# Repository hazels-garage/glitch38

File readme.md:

# glitch38

just another sweep-alike using ergogen.

## features

* choc vertical spacing, mx horizontal
* 7305 millmax socket support for hotswap switches
* inner thumb rotated 90deg and spaced for 1.5u keycap
* oled
* tenting puck support

## non-reversable
I really dislike how reversable pcbs aren't always symetric.  One mcu might be flipped, oled screen or trrs jack is slightly off.  I'll eventually do a reversable pcb as I get better and can figure out ways to do it a way that doesn't bother me.

## materials
* 2x ProMicro or equivalent
* 2x PJ-320A TRRS Jack
* 2x SSD1306 OLED Screen (optional)
* 38x 1N4148 SOD-123 Diodes
* 38x Kailh Choc v1
* 74x 7305-0-15-15-47-27-10-0 Sockets (optional)
* 36-38x 1u Kailh Choc Keycaps
* 2x 1.5u Kailh Choc Keycaps (optional, for inner thumbs)

## notes
* promicros face up. so they'd be flat against the board if installing without a socket

## firmware
QMK link goes here

## future
* later revisions will likely start to incorporate battery support and then ZMK.
* maybe give choc minis a try
* EVQ encoder support

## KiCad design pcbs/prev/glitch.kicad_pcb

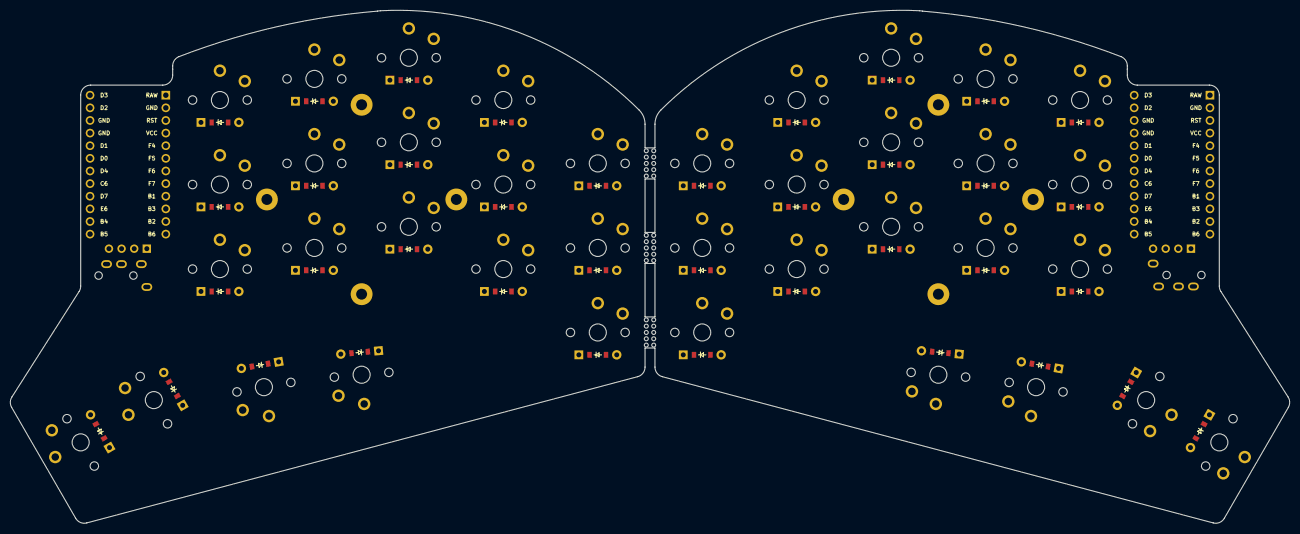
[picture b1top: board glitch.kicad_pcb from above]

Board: 2 copper layers, 257.3 x 103.2 mm, 80 parts (0 on the bottom side), 60 nets, no tracks yet.

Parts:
D1, D2, D3, D4, D5, D6, D7, D8, D9, D10, D11, D12, D13, D14, D15, D16, D17, D18, D19, D20, D21, D22, D23, D24, D25, D26, D27, D28, D29, D30, D31, D32, D33, D34, D35, D36, D37, D38: ComboDiode
MCU1, MCU2: ProMicro
OLED1, OLED2: OLED; OLED_headers
S1, S2, S3, S4, S5, S6, S7, S8, S9, S10, S11, S12, S13, S14, S15, S16, S17, S18, S19, S20, S21, S22, S23, S24, S25, S26, S27, S28, S29, S30, S31, S32, S33, S34, S35, S36, S37, S38: PG1350

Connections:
B1: D3.1, D3.2, D6.1, D6.2, D9.1, D9.2, D12.1, D12.2, D15.1, D15.2, MCU1.9, MCU2.9, S32.2, S33.2, S34.2, S38.2
B2: D1.1, D1.2, D4.1, D4.2, D7.1, D7.2, D10.1, D10.2, D13.1, D13.2, MCU1.11, MCU2.11, S20.2, S21.2, S22.2
B3: D2.1, D2.2, D5.1, D5.2, D8.1, D8.2, D11.1, D11.2, D14.1, D14.2, MCU1.10, MCU2.10, S23.2, S24.2, S25.2, S36.2
B4: D20.1, D20.2, D23.1, D23.2, D26.1, D26.2, D29.1, D29.2, D32.1, D32.2, MCU1.23, MCU2.23, S1.2, S2.2, S3.2
B5: D35.1, D35.2, D36.1, D36.2, D37.1, D37.2, D38.1, D38.2, MCU1.24, MCU2.24
B6: D16.1, D16.2, D17.1, D17.2, D18.1, D18.2, D19.1, D19.2, MCU1.12, MCU2.12
C6: MCU1.20, MCU2.20, S10.2, S11.2, S12.2, S18.2
D0: MCU1.18, MCU2.18, OLED1.3, OLED2.3
D1: MCU1.17, MCU2.17, OLED1.4, OLED2.4
D2: MCU1.14, MCU2.14
D3: MCU1.13, MCU2.13
D4: MCU1.19, MCU2.19, S7.2, S8.2, S9.2, S16.2
D7: D22.1, D22.2, D25.1, D25.2, D28.1, D28.2, D31.1, D31.2, D34.1, D34.2, MCU1.21, MCU2.21, S13.2, S14.2, S15.2, S19.2
E6: D21.1, D21.2, D24.1, D24.2, D27.1, D27.2, D30.1, D30.2, D33.1, D33.2, MCU1.22, MCU2.22, S4.2, S5.2, S6.2, S17.2
F4: MCU1.5, MCU2.5
F5: MCU1.6, MCU2.6
F6: MCU1.7, MCU2.7, S26.2, S27.2, S28.2, S35.2
F7: MCU1.8, MCU2.8, S29.2, S30.2, S31.2, S37.2
GND: MCU1.2, MCU1.15, MCU1.16, MCU2.2, MCU2.15, MCU2.16, OLED1.1, OLED2.1
RAW: MCU1.1, MCU2.1
RST: MCU1.3, MCU2.3
VCC: MCU1.4, MCU2.4, OLED1.2, OLED2.2
index_bottom: D10.1, D10.2, S10.1
index_home: D11.1, D11.2, S11.1
index_top: D12.1, D12.2, S12.1
inner_bottom: D13.1, D13.2, S13.1
inner_home: D14.1, D14.2, S14.1
inner_thumbs: D19.1, D19.2, S19.1
inner_top: D15.1, D15.2, S15.1
middle1_thumbs: D17.1, D17.2, S17.1
middle_bottom: D7.1, D7.2, S7.1
middle_home: D8.1, D8.2, S8.1
middle_thumbs: D18.1, D18.2, S18.1
middle_top: D9.1, D9.2, S9.1
mirror_index_bottom: D29.1, D29.2, S29.1
mirror_index_home: D30.1, D30.2, S30.1
mirror_index_top: D31.1, D31.2, S31.1
mirror_inner_bottom: D32.1, D32.2, S32.1
mirror_inner_home: D33.1, D33.2, S33.1
mirror_inner_thumbs: D38.1, D38.2, S38.1
mirror_inner_top: D34.1, D34.2, S34.1
mirror_middle1_thumbs: D36.1, D36.2, S36.1
mirror_middle_bottom: D26.1, D26.2, S26.1
mirror_middle_home: D27.1, D27.2, S27.1
mirror_middle_thumbs: D37.1, D37.2, S37.1
mirror_middle_top: D28.1, D28.2, S28.1
mirror_outer_thumbs: D35.1, D35.2, S35.1
mirror_pinky_bottom: D20.1, D20.2, S20.1
mirror_pinky_home: D21.1, D21.2, S21.1
mirror_pinky_top: D22.1, D22.2, S22.1
mirror_ring_bottom: D23.1, D23.2, S23.1
mirror_ring_home: D24.1, D24.2, S24.1
mirror_ring_top: D25.1, D25.2, S25.1
outer_thumbs: D16.1, D16.2, S16.1
pinky_bottom: D1.1, D1.2, S1.1
pinky_home: D2.1, D2.2, S2.1
pinky_top: D3.1, D3.2, S3.1
ring_bottom: D4.1, D4.2, S4.1
ring_home: D5.1, D5.2, S5.1
ring_top: D6.1, D6.2, S6.1

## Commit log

2022-10-17 init
2022-10-17 some cleanup
2022-11-05 Fix name
